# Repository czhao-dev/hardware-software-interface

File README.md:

# Hardware-Software Interface

A collection of systems-level projects spanning digital hardware design,
real-time operating systems, and embedded robotics. Each project is
self-contained and explores a different layer of the computing stack — from
silicon-level HDL up through real-time firmware running on physical hardware.
Read together, the three projects trace the boundary this repo is named for:
the point where software's abstractions — instructions, tasks, control loops
— meet the hardware that actually executes them. See
[How the Three Projects Relate](#how-the-three-projects-relate) for the full
thread connecting them.

## Projects

| Project | Area | Language / Tools | Description |
| --- | --- | --- | --- |
| [hardware/verilog-mini-cpu](hardware/verilog-mini-cpu) | Digital Hardware | Verilog, Python, Icarus | An 8-bit pipelined CPU with a custom 16-opcode ISA, a 2-stage IF/EX-WB pipeline, a two-pass Python assembler, and a fully self-checking testbench suite. |
| [rtos/freertos-task-scheduler](rtos/freertos-task-scheduler) | RTOS | C, FreeRTOS, POSIX | A POSIX-based FreeRTOS simulation of a smart embedded system demonstrating concurrent task scheduling, queue-based IPC, mutex-protected I/O, and runtime heap monitoring. |
| [robotics/natcar-autonomous-vehicle](robotics/natcar-autonomous-vehicle) | Embedded Robotics | C/C++, Arduino/Teensy, Eagle | An autonomous race car for the IEEE NATCAR competition: custom PCB, 128-pixel line-scan camera sensing, PD steering control, and dual PWM motor drive. |

## Repository Structure

```
hardware-software-interface/
├── README.md
├── hardware/
│   └── verilog-mini-cpu/        # 8-bit pipelined CPU (Verilog)
│       ├── src/                 # RTL modules
│       ├── tb/                  # testbenches
│       ├── tools/               # Python assembler
│       └── examples/            # assembly programs
├── rtos/
│   └── freertos-task-scheduler/ # FreeRTOS POSIX simulation (C)
│       ├── include/
│       ├── src/                 # task implementations
│       └── docs/                # architecture + setup notes
└── robotics/
    └── natcar-autonomous-vehicle/ # IEEE NATCAR race car (C/C++)
        ├── firmware/              # final + archived sketches
        ├── hardware/              # Eagle schematic and board files
        ├── docs/                  # system overview, control, calibration
        └── data/                  # inductor measurement data
```

Each project keeps its own README, build instructions, and license in its
respective directory.

## Project Deep Dives

### Verilog Mini CPU ([`hardware/verilog-mini-cpu`](hardware/verilog-mini-cpu))

This is the one project in the set with no simulator standing in for the
hardware — it's synthesizable RTL, and the pipeline hazard story is the most
interesting part of it. The 2-stage IF/EX-WB design is *hazard-free by
construction*, not by added forwarding or stalling logic: the register file
and data memory are synchronous-write/asynchronous-read, and because only one
instruction is ever resident in EX-WB at a time, instruction *i+1*'s register
reads in cycle *k+1* are guaranteed to see instruction *i*'s writeback that
committed at the clock edge ending cycle *k*. That structural guarantee is
what lets the design skip an entire class of pipeline hazard logic that a
deeper pipeline would require. Branch handling reuses the same trick for
control hazards: a single `redirect` signal, asserted by EX-WB on a taken
branch/jump/`RET`, simultaneously drives the PC mux *and* injects a NOP into
the pipeline register's input in the same cycle — no separate flush flag, no
extra state, a 1-cycle penalty by construction. The custom 16-opcode ISA
(4-bit ALU ops, immediate/branch/jump/load-store/system instruction classes)
is a compact, hand-designed ISA — small enough that its full encoding fits in
one README table, which is the point. Every module (ALU, register file, data
memory, full CPU) has its own self-checking testbench, the two-pass Python
assembler has 30 unit tests, and `loop_sum.asm` (summing 1 through 10) is
verified end-to-end against the actual simulated hardware, not just the
ISA's intended semantics.

### FreeRTOS Smart Task Scheduler ([`rtos/freertos-task-scheduler`](rtos/freertos-task-scheduler))

Six FreeRTOS tasks run concurrently on the POSIX simulator port, and the
priority assignments encode a real scheduling decision, not an arbitrary
default: the Logger task runs at priority 3 (highest), LED/Temperature/Motion
at priority 2, and Command/System-Monitor at priority 1. The logger owns every
heap-allocated log message once it's successfully enqueued and frees it after
printing — giving it the highest priority keeps that queue draining promptly
instead of letting heap-owned messages pile up behind lower-priority
producers, which would otherwise be a slow, silent heap leak under load. Three
typed queues (`ledCommandQueue`, `tempCommandQueue`, `loggerQueue`) carry
structured messages between tasks rather than raw bytes, and a single
`printMutex` serializes console output so six tasks writing concurrently never
interleave mid-line. A subtler design detail worth calling out: each
simulated-sensor task keeps its own task-local pseudo-random generator state
rather than sharing one global `rand()` call — a small thing, but it's exactly
the kind of shared-mutable-state bug that's easy to introduce and hard to
diagnose once several tasks are actually running concurrently on a real
scheduler instead of a single-threaded mental model.

### IEEE NATCAR Autonomous Race Car ([`robotics/natcar-autonomous-vehicle`](robotics/natcar-autonomous-vehicle))

NATCAR is the one project in this repo that isn't simulated or bench-tested in
isolation — it's a custom Eagle-designed PCB, a Teensy 3.1-compatible
controller, and a 128-pixel TSL1401 line-scan camera, built and tuned against
a physical track by a four-person team. The line-position estimator is a
compact edge detector: rather than thresholding the entire 128-pixel frame, it
finds the strongest rising and falling brightness transitions and averages
their positions, which is cheap enough to run every 10 ms loop iteration and
robust to lighting variation across a track. Steering is closed-loop PD
control on that position error; speed is reduced proportionally to how sharp
the turn is, and independently ramp-limited in both directions — one step per
loop coming back up after the line is reacquired, so the car doesn't snap from
a stop straight to top speed, and a 25-consecutive-lost-frame fail-safe cuts
both motors instead of driving blind. What makes the project worth reading
past the final firmware is the archive: nine iterations
(`firmware/archive/natcar_v1.1.ino` through `v1.9`) show the team starting
with three-way inductive-sensor fusion alongside the camera and progressively
simplifying down to the leaner, more reliable camera-only control loop that
shipped — a real record of an engineering team converging on what actually
worked on the track, not just the polished end state.

## How the Three Projects Relate

The three projects aren't grouped here by coincidence — each one sits at a
different point along the boundary this repo is named for, the point where
software's abstractions meet the hardware that actually executes them:

1. **`verilog-mini-cpu` is the hardware side made explicit.** Gates, a
   register file, and a pipeline register realize an instruction set directly
   in synthesizable RTL — there is no layer of software standing between the
   instruction encoding and the physical logic that executes it.
2. **`freertos-task-scheduler` builds on top of that.** An RTOS assumes the
   ISA-level guarantees below it hold, and adds the next layer of abstraction
   software actually needs: concurrent tasks, queues, priorities, and
   scheduling — coordinating several pieces of software sharing one
   processor, entirely in a POSIX simulation with no physical hardware in the
   loop.
3. **`natcar-autonomous-vehicle` is where software reaches back out through
   that boundary.** A PD control loop reading a real camera and writing real
   PWM signals is software touching physical hardware at the other end of the
   stack — voltages and timing, not architectural state.

There's a second thread worth naming: two of the three projects are
simulate-and-verify-on-a-dev-machine by design (self-checking Verilog
testbenches for every module, a POSIX simulation of the RTOS with zero
application warnings), while NATCAR is the one project actually deployed
against physical reality — and its firmware archive is the record of what
changed once simulation gave way to a real track, real sensors, and real
noise.

## Skills and Concepts Covered

| Layer | Concepts |
| --- | --- |
| Digital Logic / RTL | Verilog, pipelined datapath, hazard analysis, ALU design, synchronous vs. asynchronous read/write |
| Systems Programming | C, memory layout, bit manipulation, signed/unsigned arithmetic |
| Real-Time Systems | FreeRTOS task scheduling, queues, mutexes, heap management, POSIX threading |
| Embedded Hardware | PCB design (Eagle), Teensy/Arduino, servo and motor PWM, analog sensor front ends |
| Verification & Testing | Unit tests, integration tests, self-checking testbenches, waveform capture (VCD/GTKWave) |
| Toolchain | Python assembler, GNU Make, Icarus Verilog, custom test harnesses |

## Quick Start

Each project has its own build prerequisites; see the individual READMEs for
full setup instructions. At a glance:

```bash
# FreeRTOS Task Scheduler (requires FreeRTOS kernel sources at ./FreeRTOS)
cd rtos/freertos-task-scheduler
make && ./freertos_sim

# Verilog Mini CPU (requires Icarus Verilog and Python 3)
cd hardware/verilog-mini-cpu
make test        # run all Verilog + assembler tests
make test-program  # assemble loop_sum.asm and simulate end-to-end

# NATCAR Firmware (requires Arduino IDE with Teensyduino)
# Open robotics/natcar-autonomous-vehicle/firmware/natcar_final/natcar_final.ino
```

## References

**FreeRTOS Task Scheduler**
- [FreeRTOS Kernel](https://github.com/FreeRTOS/FreeRTOS-Kernel) — source of the RTOS kernel and POSIX simulator port used in this project.
- [FreeRTOS Reference Manual](https://www.freertos.org/Documentation/RTOS_book.html) — API reference for tasks, queues, mutexes, and timers.

**Verilog Mini CPU**
- [Icarus Verilog](https://steveicarus.github.io/iverilog/) — open-source Verilog simulator used for all testbenches.
- [GTKWave](https://gtkwave.sourceforge.net/) — waveform viewer for VCD output from the integration testbenches.

**IEEE NATCAR Autonomous Vehicle**
- [TSL1401-DB Line-Scan Camera Datasheet](robotics/natcar-autonomous-vehicle/references/28317-TSL1401-DB-Manual.pdf) — timing diagrams and electrical specs for the 128-pixel optical sensor.
- [IEEE NATCAR Competition](https://ieee.ucdavis.edu/natcar/) — competition rules and track specifications.

## License

This index repo is licensed under the MIT License — see [LICENSE](LICENSE).
Each subproject carries its own license in its own directory (the FreeRTOS
task scheduler, Verilog mini CPU, and NATCAR vehicle are each Apache License
2.0) — check the subproject's own `LICENSE` file before reusing its code.

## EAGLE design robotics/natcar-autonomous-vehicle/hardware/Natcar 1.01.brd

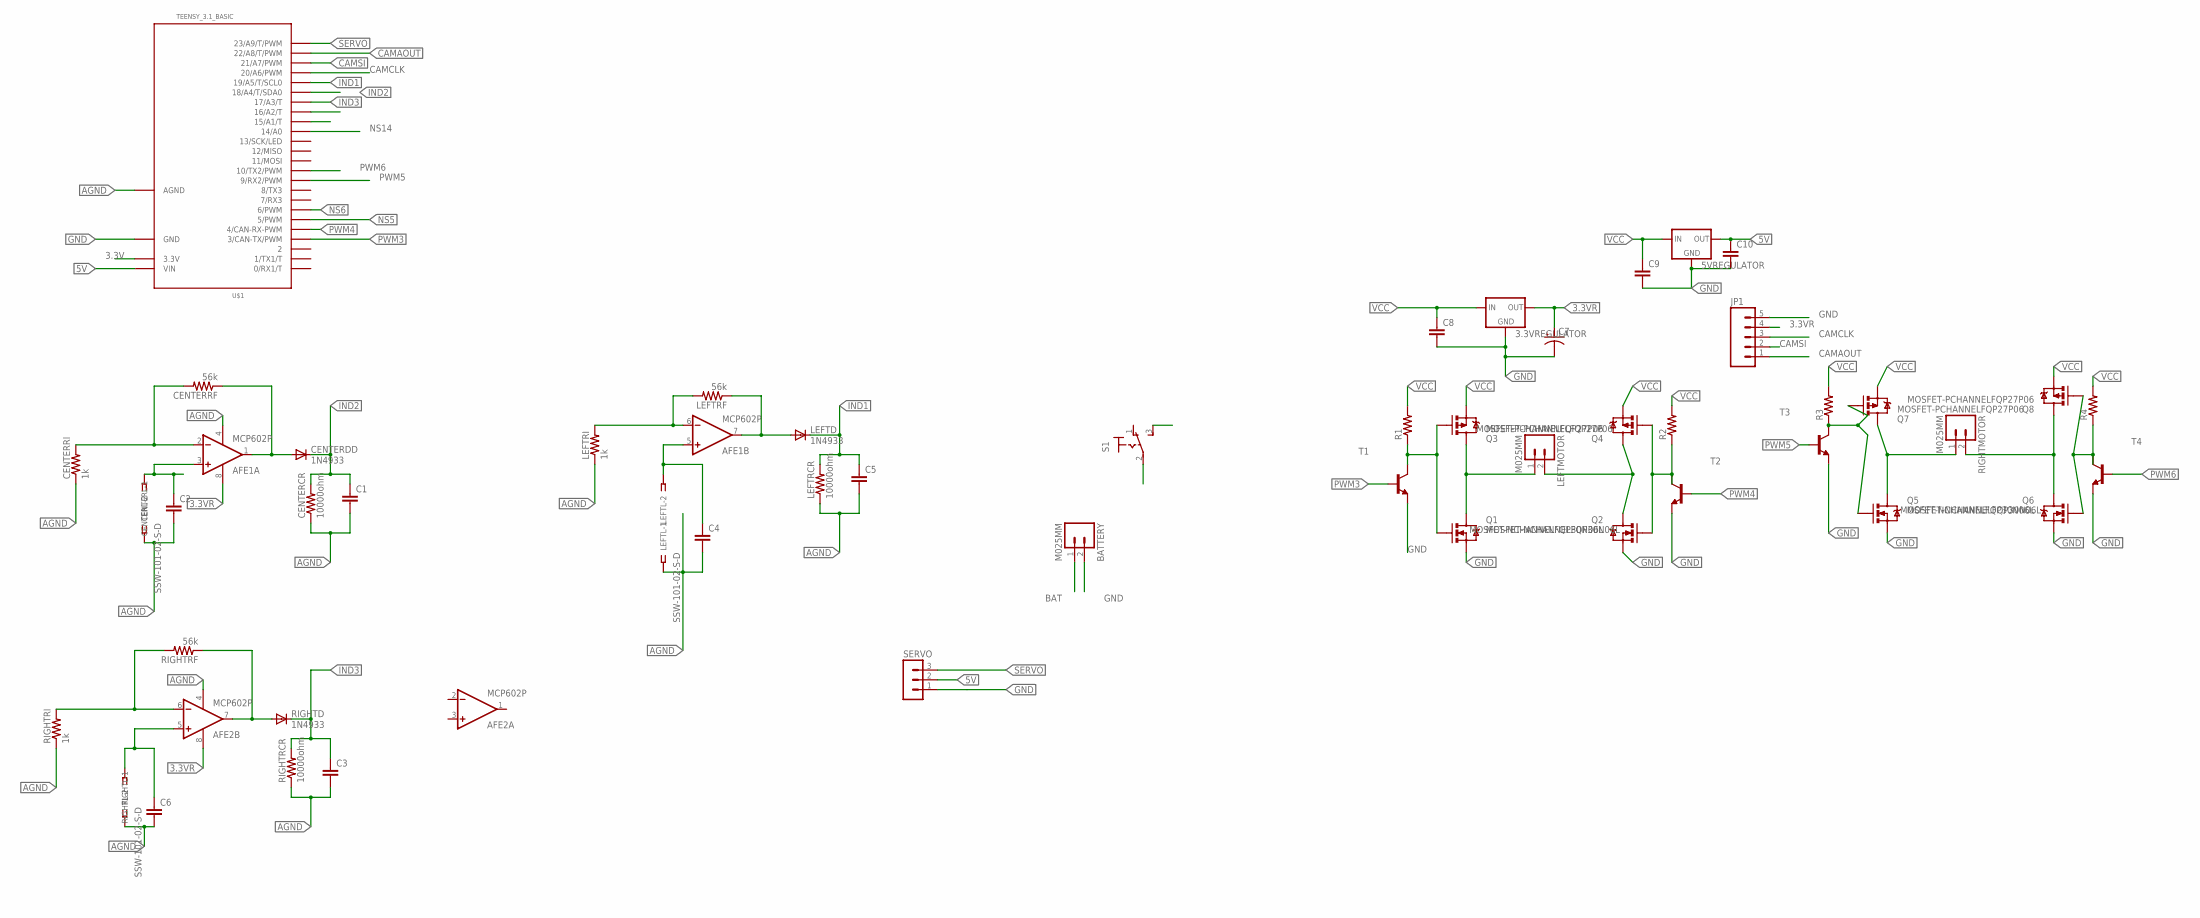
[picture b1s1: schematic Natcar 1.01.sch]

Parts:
3.3VREGULATOR, 5VREGULATOR: V_REG_78XXSINK; TO220-IGO
AFE1, AFE2: MCP602P; DIL08
BATTERY: M025MM; SCREWTERMINAL-5MM-2
C1, C2, C3, C4, C5, C6: CAPEZ; CAP-PTH-SMALLEZ
C7: CAP_POLPTH2; CPOL-RADIAL-10UF-25V
C8, C9, C10: CAPPTH2; CAP-PTH-SMALL2
CENTERCR: 10000ohm; 0204/5
CENTERDD: 1N4933; DO41-10
CENTERL: SSW-101-02-S-D
CENTERRF: 56k; 0204/5
CENTERRI: 1k; 0204/5
JP1: M05PTH; 1X05
LEFTD: 1N4933; DO41-10
LEFTL: SSW-101-02-S-D
LEFTMOTOR: M025MM; SCREWTERMINAL-5MM-2
LEFTRCR: 10000ohm; 0204/5
LEFTRF: 56k; 0204/5
LEFTRI: 1k; 0204/5
Q1, Q2, Q5, Q6: MOSFET-NCHANNELFQP30N06L; TO220V
Q3, Q4, Q7, Q8: MOSFET-PCHANNELFQP27P06; TO220V
R1, R2, R3, R4: R-US_0204/5; 0204/5
RIGHTD: 1N4933; DO41-10
RIGHTL: SSW-101-02-S-D
RIGHTMOTOR: M025MM; SCREWTERMINAL-5MM-2
RIGHTRCR: 10000ohm; 0204/5
RIGHTRF: 56k; 0204/5
RIGHTRI: 1k; 0204/5
S1: 320-916
SERVO: MA03-1
T1, T2, T3, T4: -NPN-TO92-EBC; TO92-EBC
U$1: TEENSY_3.1_BASIC

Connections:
3.3V: U$1.3.3V
3.3VR: 3.3VREGULATOR.OUT, AFE1.8 (V+), AFE2.8 (V+), C7.1 (+), JP1.4
5V: 5VREGULATOR.OUT, C10.1, SERVO.2, U$1.VIN
AGND: AFE1.4 (V-), AFE2.4 (V-), C1.2, C2.2, C3.2, C4.2, C5.2, C6.2, CENTERCR.1, CENTERL.1, CENTERRI.1, LEFTL.1, LEFTRCR.1, LEFTRI.1, RIGHTL.1, RIGHTRCR.1, RIGHTRI.1, U$1.AGND
BAT: BATTERY.1, S1.3 (S)
CAMAOUT: JP1.1, U$1.22/A8 (22/A8/T/PWM)
CAMCLK: JP1.3, U$1.20/A6 (20/A6/PWM)
CAMSI: JP1.2, U$1.21/A7 (21/A7/PWM)
GND: 3.3VREGULATOR.GND, 5VREGULATOR.GND, BATTERY.2, C7.2 (-), C8.2, C9.2, C10.2, JP1.5, Q1.3 (S), Q2.3 (S), Q5.3 (S), Q6.3 (S), SERVO.1, T1.E, T2.E, T3.E, T4.E, U$1.GND
IND1: C5.1, LEFTD.C, LEFTRCR.2, U$1.19/A5 (19/A5/T/SCL0)
IND2: C1.1, CENTERCR.2, CENTERDD.C, U$1.18/A4 (18/A4/T/SDA0)
IND3: C3.1, RIGHTD.C, RIGHTRCR.2, U$1.17/A3 (17/A3/T)
unnamed: LEFTMOTOR.2, Q2.2 (D), Q4.2 (D)
unnamed: Q2.1 (G), Q4.1 (G), R2.1, T2.C
unnamed: Q5.2 (D), Q7.2 (D), RIGHTMOTOR.1
unnamed: Q6.2 (D), Q8.2 (D), RIGHTMOTOR.2
unnamed: Q1.1 (G), Q3.1 (G), R1.1, T1.C
unnamed: Q5.1 (G), Q7.1 (G), R3.1, T3.C
unnamed: Q6.1 (G), Q8.1 (G), R4.1, T4.C
unnamed: LEFTMOTOR.1, Q1.2 (D), Q3.2 (D)
unnamed: AFE2.6 (-IN), RIGHTRF.2, RIGHTRI.2
unnamed: AFE2.7 (OUT), RIGHTD.A, RIGHTRF.1
unnamed: AFE1.2 (-IN), CENTERRF.2, CENTERRI.2
unnamed: AFE1.3 (+IN), C2.1, CENTERL.2
unnamed: AFE2.5 (+IN), C6.1, RIGHTL.2
unnamed: AFE1.1 (OUT), CENTERDD.A, CENTERRF.1
unnamed: AFE1.7 (OUT), LEFTD.A, LEFTRF.1
unnamed: AFE1.5 (+IN), C4.1, LEFTL.2
unnamed: AFE1.6 (-IN), LEFTRF.2, LEFTRI.2
NS5: U$1.5 (5/PWM)
NS6: U$1.6 (6/PWM)
NS14: U$1.14/A0
PWM3: T1.B, U$1.3 (3/CAN-TX/PWM)
PWM4: T2.B, U$1.4 (4/CAN-RX-PWM)
PWM5: T3.B, U$1.9 (9/RX2/PWM)
PWM6: T4.B, U$1.10 (10/TX2/PWM)
SERVO: SERVO.3, U$1.23/A9 (23/A9/T/PWM)
VCC: 3.3VREGULATOR.IN, 5VREGULATOR.IN, C8.1, C9.1, Q3.3 (S), Q4.3 (S), Q7.3 (S), Q8.3 (S), R1.2, R2.2, R3.2, R4.2, S1.2

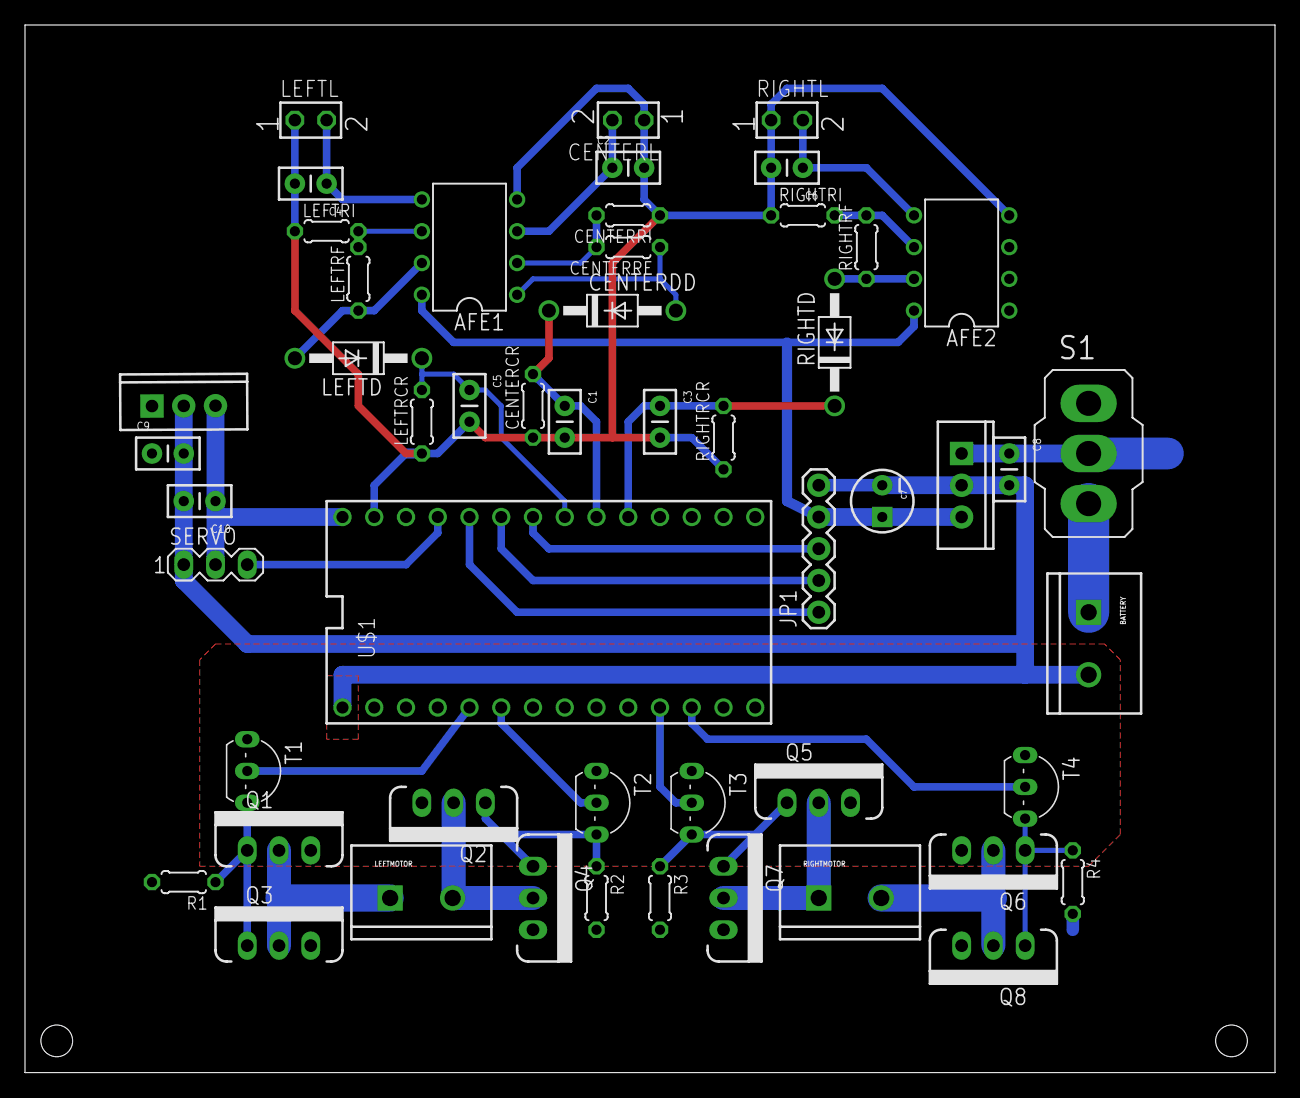
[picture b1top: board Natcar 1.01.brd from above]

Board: 2 copper layers, 100.0 x 83.8 mm, 52 parts (0 on the bottom side), 34 nets.

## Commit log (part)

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2025-05-25 Add arduino files for line detection algorithms
2025-06-04 Create Makefile
2025-06-04 Add control_unit.v register_file.v and top.v files
2025-06-07 Add main.c and Makefile
2025-06-07 Add header files
2025-06-07 Add source files
2025-06-07 Update LICENSE
2026-05-08 Create data_test
2026-05-08 Add inductor data
2026-05-08 Create docs_test
2026-05-08 Add document files
2026-05-08 Create hardware_test
2026-05-08 Move Natcar 1.01.brd to hardware/Natcar 1.01.brd
2026-05-08 Move Natcar 1.01.sch to hardware/Natcar 1.01.sch
2026-05-08 Create images_test
2026-05-08 Add schematic images
2026-05-08 Create references_test
2026-05-08 Add Line Scan Camera Manual
2026-05-08 Move natcar_v1.1.ino to firmware/archive/natcar_v1.1.ino
2026-05-08 Rename natcar_v1.2.ino to firmware/archive/natcar_v1.2.ino
2026-05-08 Move natcar_v1.3.ino to firmware/archive/natcar_v1.3.ino
2026-05-08 Move natcar_v1.4.ino to firmware/archive/natcar_v1.4.ino
2026-05-08 Move natcar_v1.5.ino to firmware/archive/natcar_v1.5.ino
2026-05-08 Move natcar_v1.6.ino to firmware/archive/natcar_v1.6.ino
2026-05-08 Move natcar_v1.8.ino to firmware/archive/natcar_v1.8.ino
2026-05-08 Move natcar_v1.9.ino to firmware/archive/natcar_v1.9.ino
2026-05-08 Add natcar_final.ino for autonomous car control
2026-05-08 Revise README for clarity and detail
2026-05-08 Enhance line detection and motor control logic
2026-05-08 Enhance line detection and motor control logic
    Added constants for edge detection and motor control. Implemented logic to handle lost line frames and adjusted motor speed accordingly.
2026-05-08 Update control algorithm documentation with new parameters
    Added new parameters for line detection thresholds and fail-safe behavior.
2026-05-08 Update control algorithm documentation with new parameters
2026-05-08 Update firmware history and add natcar_v1.9.ino
    Added natcar_v1.9.ino to the firmware history and clarified minimum PWM description.
2026-05-08 Add new configuration parameters to README
2026-05-08 Add excel data
2026-05-08 Add architecture documentation for embedded system simulation
2026-05-08 Add SETUP.md file
2026-05-08 Format command_task.h header guards and comments
2026-05-08 Create FreeRTOSConfig.h with configuration options
    Add FreeRTOS configuration header with default settings.
2026-05-08 Create FreeRTOSConfig.h with configuration options
2026-05-08 Format led_task.h header guard and comments
2026-05-08 Format logger_task.h header guards and comments
2026-05-08 Format motion_task.h header file
2026-05-08 Enhance shared_defs.h with command types and limits
2026-05-08 Reformat system_monitor.h header file
2026-05-08 Remove unnecessary whitespace in temp_task.h
2026-05-08 Enhance utils.h with logging and PRNG functions
2026-05-08 Enhance utils.h with logging and PRNG functions
    Added new logging and random number generation functions.
2026-05-08 Enhance command task with LED control and logging
2026-05-08 Enhance command task with LED control and logging
    Refactor command task to include LED period adjustments and improve logging.
2026-05-08 Refactor LED task for command handling and state management
2026-05-08 Enhance logger task with null checks and safety
2026-05-08 Refactor main function for error handling and registry
    Updated queue creation and task initialization with error handling and registry addition.
2026-05-08 Refactor main function for error handling and registry
2026-05-08 Refactor motion detection task for improved randomness
2026-05-08 Refactor system monitor task with shared_defs.h
2026-05-08 Refactor temperature task for improved functionality
    Refactor temperature task to improve sampling and threshold handling. Introduce clamping for threshold values and separate functions for temperature sampling and threshold updates.
2026-05-08 Refactor temperature task for improved functionality
2026-05-08 Refactor utility functions for better safety and logging
2026-05-08 Update Makefile for improved build process
    Refactor Makefile for FreeRTOS project structure and dependencies.
2026-05-08 Update Makefile for improved build process
2026-05-08 Revise README for improved clarity and organization
    Updated README to enhance clarity and structure, including features, repository layout, task overview, and build instructions.
2026-05-08 Revise README for improved clarity and organization
2026-05-09 Enhance ALU with carry, overflow, and negative flags
2026-05-09 Refactor control unit to use instruction input
2026-05-09 Refactor register file to support multiple registers
2026-05-09 Redesign top module for enhanced CPU functionality
2026-05-09 Add instruction_memory.v
2026-05-09 Refactor top_tb.v for improved testbench structure
2026-05-09 Add register_file_tb.v and alu_tb.v
2026-05-09 Enhance Makefile with build and test structure
2026-05-09 Add requirements checklist for FreeRTOS project
2026-05-09 Add requirements section to README
    Added a requirements section to outline project dependencies.
2026-05-09 Add requirements section to README
2026-05-09 Update README to remove requirements.txt mention
2026-05-10 Rename section from 'Why This Is Useful' to 'Project Highlights'
2026-05-10 Remove future improvements section
2026-06-12 Harden line-following control loop in final firmware
2026-06-12 Add .gitignore and remove dead run-time-stats macros
2026-06-12 Add branch/jump and load/store support, clean up dead code
2026-06-15 Widen datapath to 8-bit and implement ISA v2
2026-06-15 Widen datapath to 8-bit and implement ISA v2
    Expands registers/ALU/memories from 4-bit to 8-bit, adds 8 new ALU
    ops (NOT/NEG/ROL/ROR/MUL/NAND/INC/DEC), an accumulator-style ALU-IMM
    instruction class with LDI, and JAL/RET/HALT via a new R7 link
    register and halted output. All testbenches rewritten for the new
    encodings and widths.
2026-06-16 Add 2-stage pipeline (Phase 2) and Python assembler toolchain (Phase 3)
    Phase 2 — pipelined CPU:
    - Add src/if_exwb_reg.v: IF/EX-WB pipeline register with reset-to-NOP
    and redirect-driven flush; gives a 1-cycle branch penalty with no
    separate flush flag
    - Restructure src/top.v into IF / EX-WB stages; redirect signal drives
    both the PC mux and the pipeline-register input mux simultaneously
2026-06-16 Add 2-stage pipeline (Phase 2) and Python assembler toolchain (Phase 3)
2026-06-16 Remove Python cache from tracking; add __pycache__ to .gitignore
2026-06-18 Polish README for portfolio presentation
2026-06-18 Add badges, table of contents, GFLOP/s metric, and license section to README
2026-06-18 Polish README with badges, architecture image, and table of contents
2026-06-18 Polish README with badges, tech stack, and test results
2026-06-18 Polish README with badges, tech stack, and test results
    Add language/RTOS/platform/build/license badges and a Tech Stack
    section for portfolio readability, plus a Testing & Results section
    with real simulator output captured from a local run.
2026-06-19 Add MIT License to the project
2026-06-19 Add project README
2026-06-19 Implement RV32I simulator core, CLI, examples, and tests
2026-06-20 Migrate simulator from Python to C++17
    Port the RV32I core, CLI, encoder/decoder, and 42-test suite to C++,
    building with CMake. Behavior is verified bit-for-bit identical to the
    Python implementation (example binaries regenerate byte-for-byte, all
    ported tests pass).
2026-06-20 Migrate simulator from Python to C++17
2026-06-23 Remove Development Roadmap section from README
2026-06-25 Add root README describing repo structure
2026-06-25 Add root README describing repo structure
    Organizes the five existing project repos (cuda, riscv, rtos,
    hardware, robotics) under topic-based directories, each merged in
    via git subtree to preserve their original commit history.
2026-06-25 Remove cuda/matmul-optimizer from the lab
2026-06-25 Remove cuda/matmul-optimizer from the lab
    Drop the CUDA matmul project from this repo and update the root
    README's project table and structure diagram accordingly.
2026-06-27 docs: expand README with highlights, skills table, quick start
2026-06-27 docs: expand top-level README with highlights, skills table, and quick start
2026-06-27 docs: add References section to top-level README

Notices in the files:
README.md:
License: MIT
parts and their libraries:
SparkFun-PowerIC: Licensing: Creative Commons ShareAlike 4.0 International - https://creativecommons.org/licenses/by-sa/4.0
